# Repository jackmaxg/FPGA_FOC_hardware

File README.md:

# FPGA_FOC_hardware
Hardware for the 6.111 FPGA_FOC project

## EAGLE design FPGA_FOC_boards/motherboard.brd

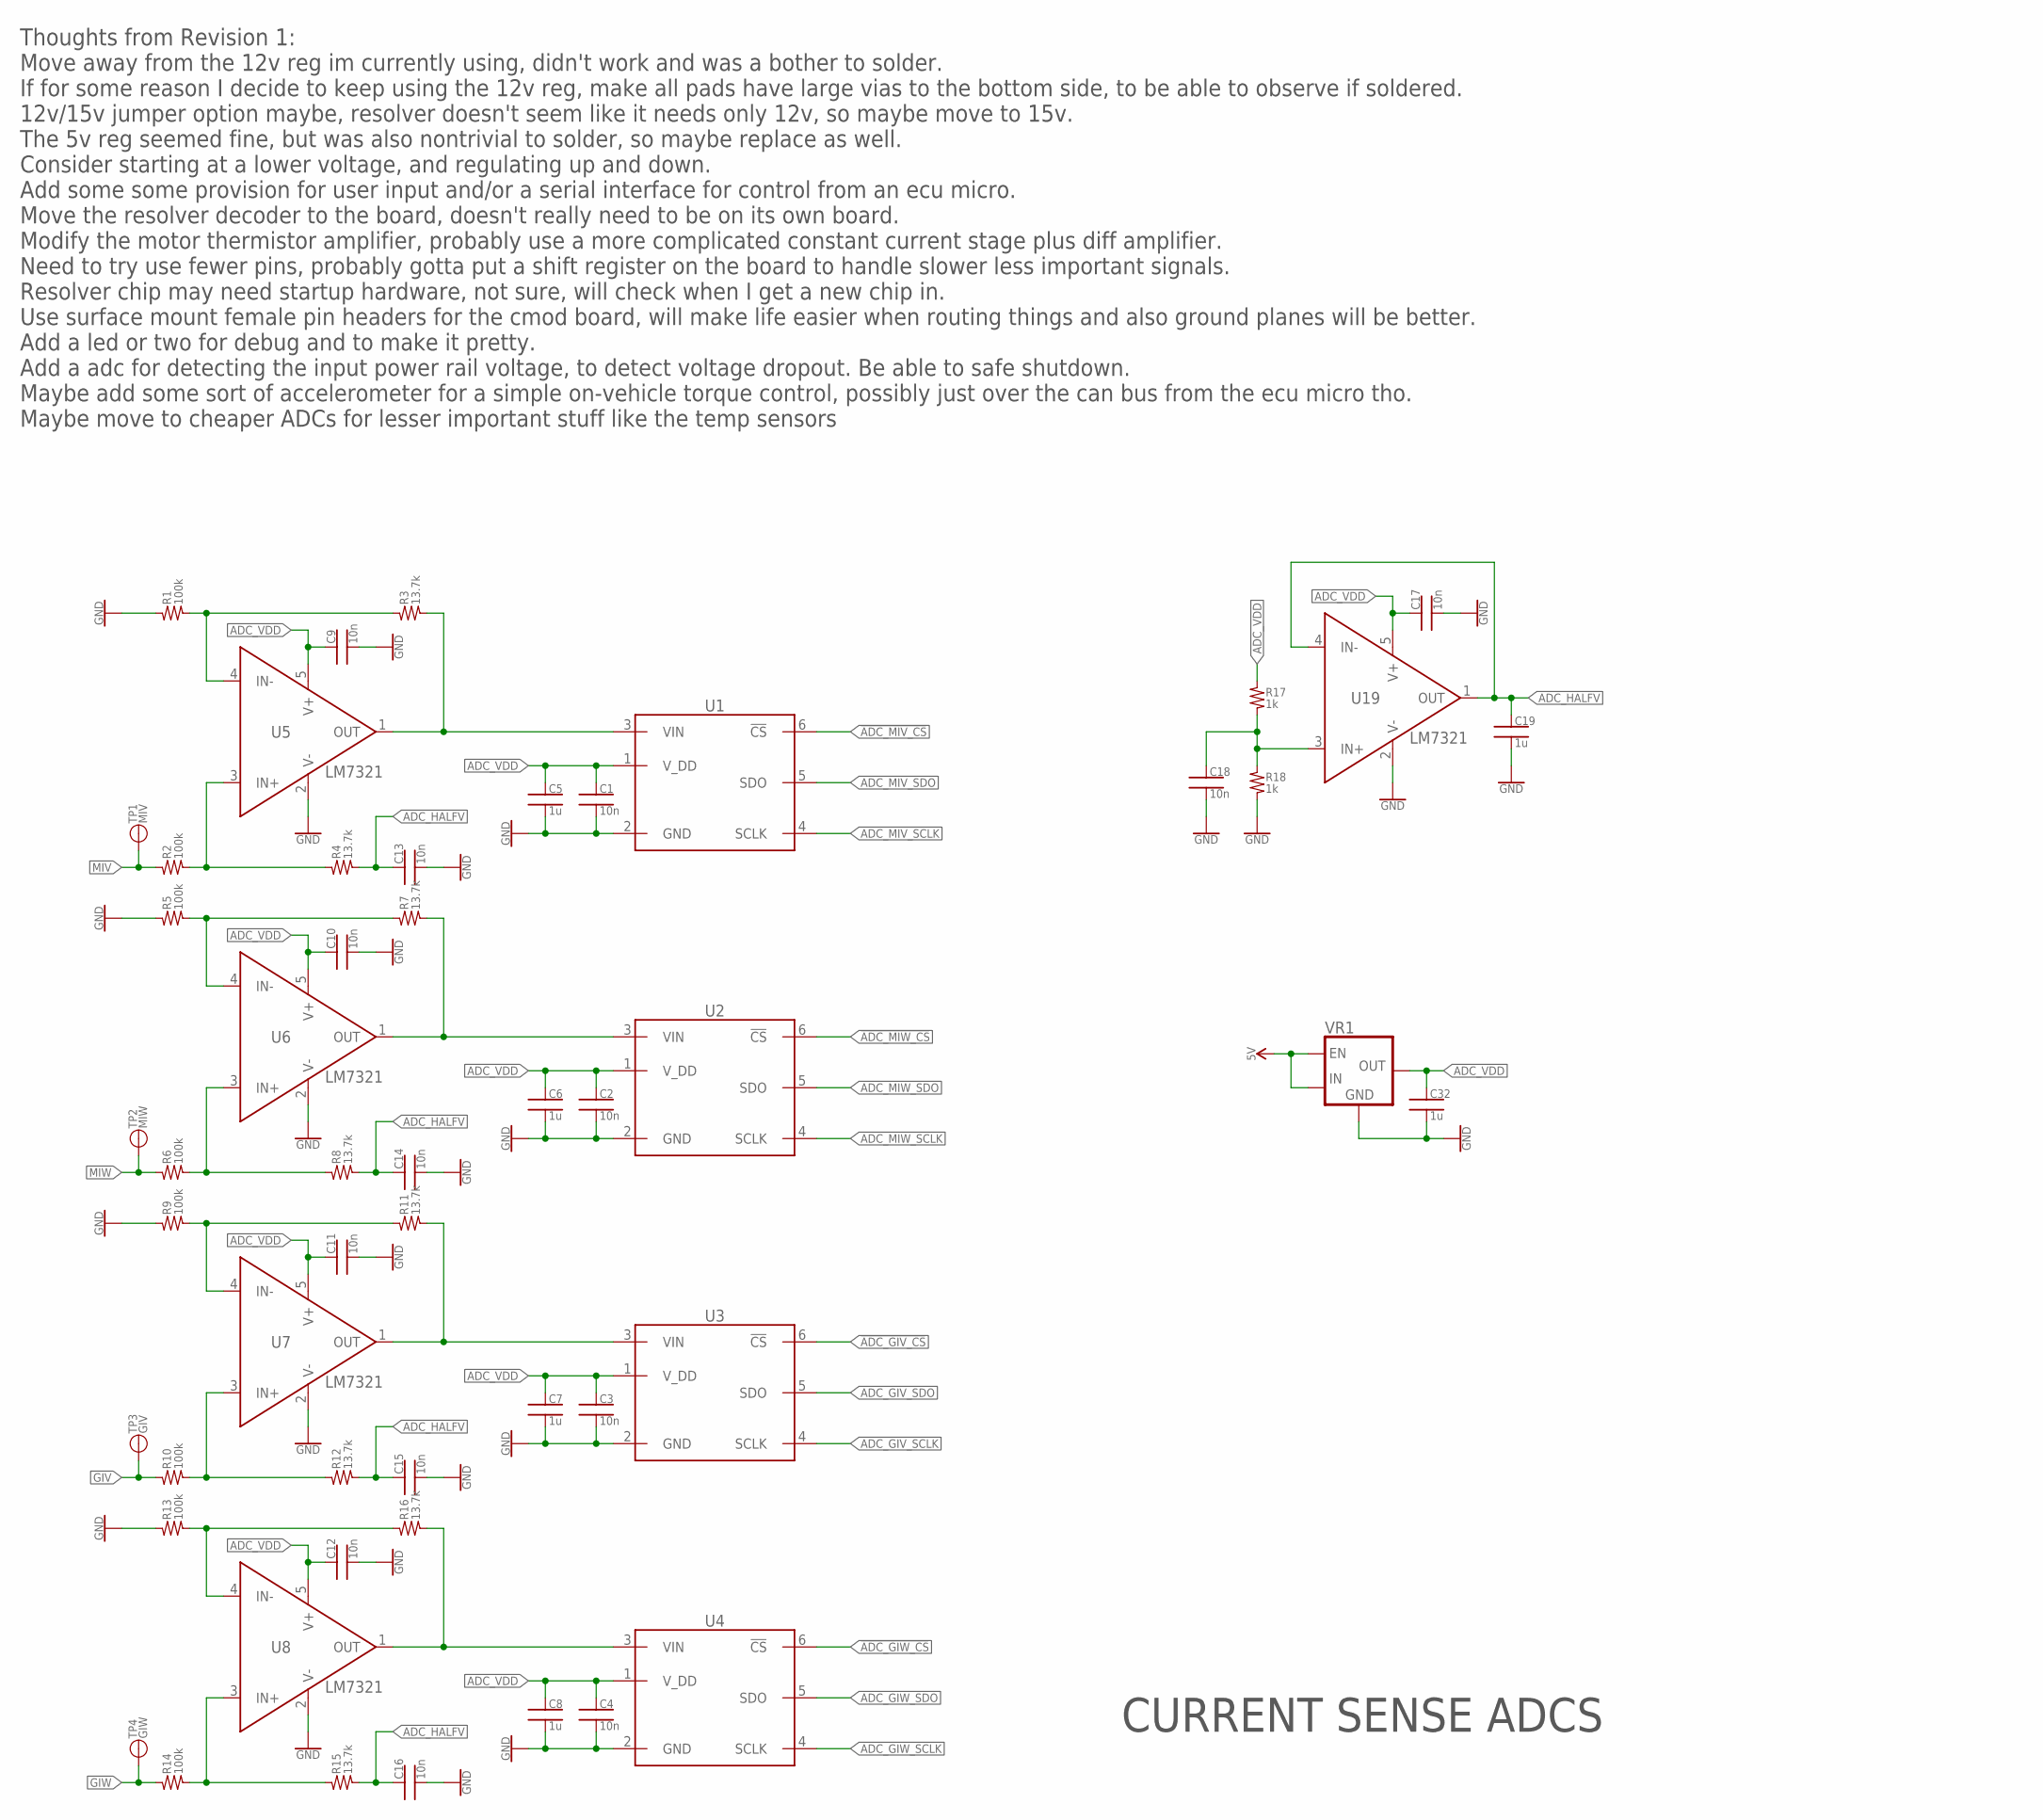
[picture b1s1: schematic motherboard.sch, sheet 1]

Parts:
C1, C2, C3, C4, C9, C10, C11, C12, C13, C14, C15, C16, C17, C18: 10n; 0402
C5, C6, C7, C8, C19, C32: 1u; 0402
R1, R2, R5, R6, R9, R10, R13, R14: 100k; 0402
R3, R4, R7, R8, R11, R12, R15, R16: 13.7k; 0402
R17, R18: 1k; 0402
TP1: MIV; 1X01_50MIL
TP2: MIW; 1X01_50MIL
TP3: GIV; 1X01_50MIL
TP4: GIW; 1X01_50MIL
U1, U2, U3, U4: ADS7883; SOT23-6
U5, U6, U7, U8, U19: LM7321; SOT23-5
VR1: TLV733P_SOT23; SOT23-5

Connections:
5V: VR1.1 (IN), VR1.3 (EN); also elsewhere on the board
!ADC_GIV_CS: U3.6 (!CS); also elsewhere on the board
!ADC_GIW_CS: U4.6 (!CS); also elsewhere on the board
!ADC_MIV_CS: U1.6 (!CS); also elsewhere on the board
!ADC_MIW_CS: U2.6 (!CS); also elsewhere on the board
ADC_GIV_SCLK: U3.4 (SCLK); also elsewhere on the board
ADC_GIV_SDO: U3.5 (SDO); also elsewhere on the board
ADC_GIW_SCLK: U4.4 (SCLK); also elsewhere on the board
ADC_GIW_SDO: U4.5 (SDO); also elsewhere on the board
ADC_HALFV: C13.1, C14.1, C15.1, C16.1, C19.1, R4.2, R8.2, R12.2, R15.2, U19.1 (OUT), U19.4 (IN-)
ADC_HALFV_REF: C18.1, R17.2, R18.1, U19.3 (IN+)
ADC_MIV_SCLK: U1.4 (SCLK); also elsewhere on the board
ADC_MIV_SDO: U1.5 (SDO); also elsewhere on the board
ADC_MIW_SCLK: U2.4 (SCLK); also elsewhere on the board
ADC_MIW_SDO: U2.5 (SDO); also elsewhere on the board
ADC_VDD: C1.1, C2.1, C3.1, C4.1, C5.1, C6.1, C7.1, C8.1, C9.1, C10.1, C11.1, C12.1, C17.1, C32.1, R17.1, U1.1 (V_DD), U2.1 (V_DD), U3.1 (V_DD), U4.1 (V_DD), U5.5 (V+), U6.5 (V+), U7.5 (V+), U8.5 (V+), U19.5 (V+), VR1.5 (OUT); also elsewhere on the board
GIV: R10.1, TP3.1; also elsewhere on the board
GIW: R14.1, TP4.1; also elsewhere on the board
GND: C1.2, C2.2, C3.2, C4.2, C5.2, C6.2, C7.2, C8.2, C9.2, C10.2, C11.2, C12.2, C13.2, C14.2, C15.2, C16.2, C17.2, C18.2, C19.2, C32.2, R1.1, R5.1, R9.1, R13.1, R18.2, U1.2 (GND), U2.2 (GND), U3.2 (GND), U4.2 (GND), U5.2 (V-), U6.2 (V-), U7.2 (V-), U8.2 (V-), U19.2 (V-), VR1.2 (GND), VR1.4 (GND); also elsewhere on the board
MIV: R2.1, TP1.1; also elsewhere on the board
MIW: R6.1, TP2.1; also elsewhere on the board
U5_IN+: R2.2, R4.1, U5.3 (IN+)
U5_IN-: R1.2, R3.1, U5.4 (IN-)
U5_OUT: R3.2, U1.3 (VIN), U5.1 (OUT)
U6_IN+: R6.2, R8.1, U6.3 (IN+)
U6_IN-: R5.2, R7.1, U6.4 (IN-)
U6_OUT: R7.2, U2.3 (VIN), U6.1 (OUT)
U7_IN+: R10.2, R12.1, U7.3 (IN+)
U7_IN-: R9.2, R11.1, U7.4 (IN-)
U7_OUT: R11.2, U3.3 (VIN), U7.1 (OUT)
U8_IN+: R14.2, R15.1, U8.3 (IN+)
U8_IN-: R13.2, R16.1, U8.4 (IN-)
U8_OUT: R16.2, U4.3 (VIN), U8.1 (OUT)

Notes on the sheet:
CURRENT SENSE ADCS
Thoughts from Revision 1: Move away from the 12v reg im currently using, didn't work and was a bother to solder. If for some reason I decide to keep using the 12v reg, make all pads have large vias to the bottom side, to be able to observe if soldered. 12v/15v jumper option maybe, resolver doesn't 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

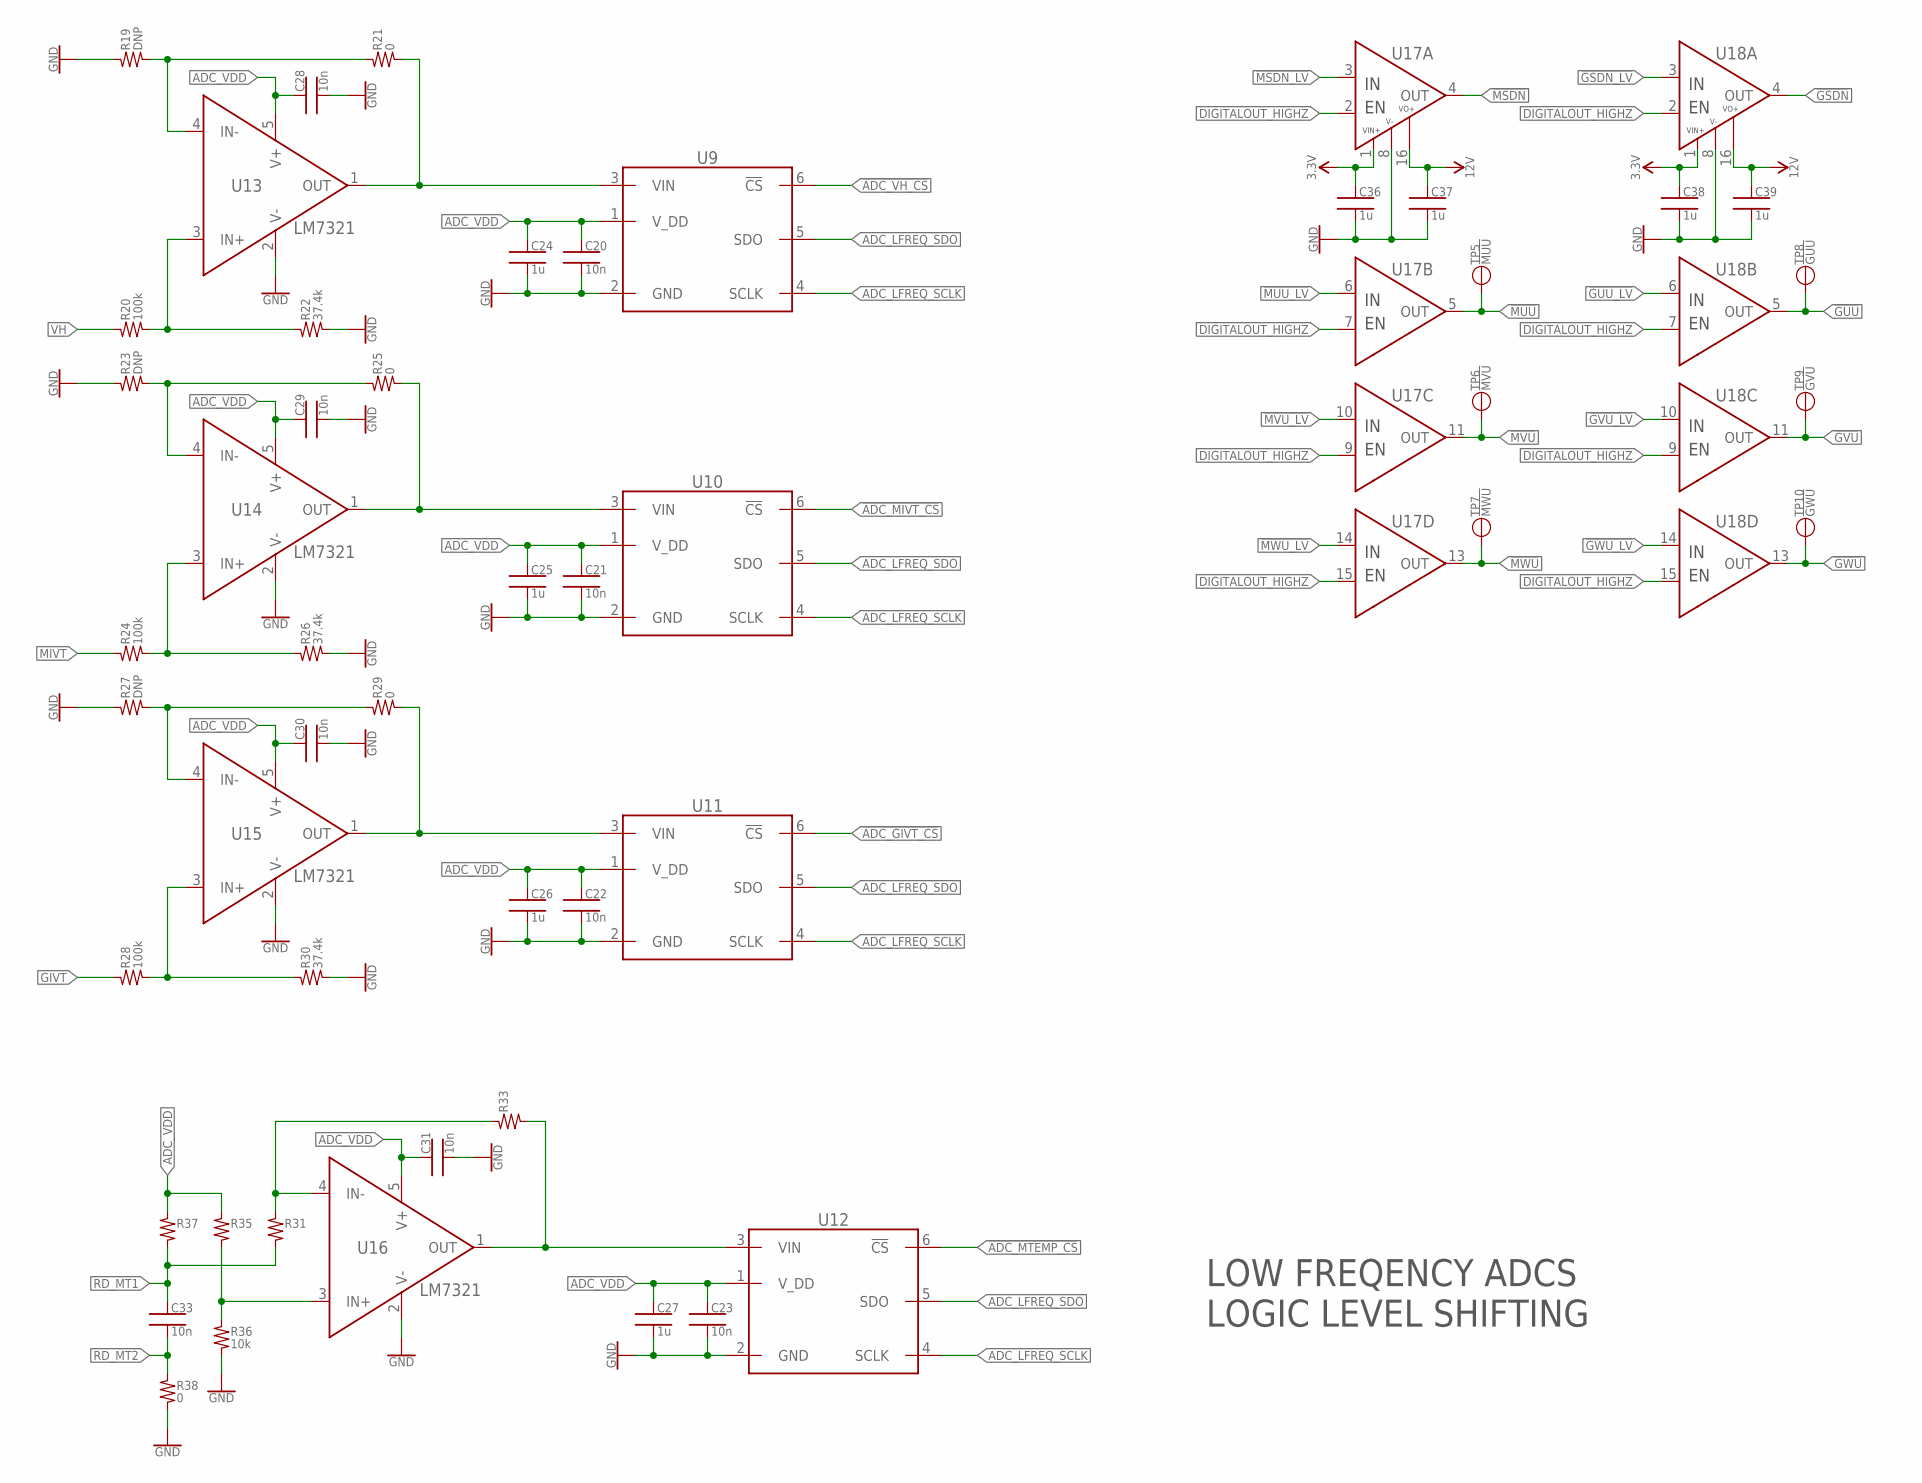
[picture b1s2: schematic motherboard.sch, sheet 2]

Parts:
C20, C21, C22, C23, C28, C29, C30, C31, C33: 10n; 0402
C24, C25, C26, C27, C36, C37, C38, C39: 1u; 0402
R19, R23, R27: DNP; 0402
R20, R24, R28: 100k; 0402
R21, R25, R29, R38: 0; 0402
R22, R26, R30: 37.4k; 0402
R31, R33, R35, R37: RES_SMD_0402; 0402
R36: 10k; 0402
TP5: !MUU; 1X01_50MIL
TP6: !MVU; 1X01_50MIL
TP7: !MWU; 1X01_50MIL
TP8: !GUU; 1X01_50MIL
TP9: !GVU; 1X01_50MIL
TP10: !GWU; 1X01_50MIL
U9, U10, U11, U12: ADS7883; SOT23-6
U13, U14, U15, U16: LM7321; SOT23-5
U17, U18: CD40109BPWR; TSSOP-16

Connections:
3.3V: C36.1, C38.1, U17.1 (VIN+), U18.1 (VIN+); also elsewhere on the board
12V: C37.1, C39.1, U17.16 (VOUT+), U18.16 (VOUT+); also elsewhere on the board
!ADC_GIVT_CS: U11.6 (!CS); also elsewhere on the board
!ADC_MIVT_CS: U10.6 (!CS); also elsewhere on the board
!ADC_MTEMP_CS: U12.6 (!CS); also elsewhere on the board
!ADC_VH_CS: U9.6 (!CS); also elsewhere on the board
!GSDN: U18.4 (OUT); also elsewhere on the board
!GSDN_LV: U18.3 (IN); also elsewhere on the board
!GUU: TP8.1, U18.5 (OUT); also elsewhere on the board
!GUU_LV: U18.6 (IN); also elsewhere on the board
!GVU: TP9.1, U18.11 (OUT); also elsewhere on the board
!GVU_LV: U18.10 (IN); also elsewhere on the board
!GWU: TP10.1, U18.13 (OUT); also elsewhere on the board
!GWU_LV: U18.14 (IN); also elsewhere on the board
!MSDN: U17.4 (OUT); also elsewhere on the board
!MSDN_LV: U17.3 (IN); also elsewhere on the board
!MUU: TP5.1, U17.5 (OUT); also elsewhere on the board
!MUU_LV: U17.6 (IN); also elsewhere on the board
!MVU: TP6.1, U17.11 (OUT); also elsewhere on the board
!MVU_LV: U17.10 (IN); also elsewhere on the board
!MWU: TP7.1, U17.13 (OUT); also elsewhere on the board
!MWU_LV: U17.14 (IN); also elsewhere on the board
ADC_LFREQ_SCLK: U9.4 (SCLK), U10.4 (SCLK), U11.4 (SCLK), U12.4 (SCLK); also elsewhere on the board
ADC_LFREQ_SDO: U9.5 (SDO), U10.5 (SDO), U11.5 (SDO), U12.5 (SDO); also elsewhere on the board
ADC_VDD: C20.1, C21.1, C22.1, C23.1, C24.1, C25.1, C26.1, C27.1, C28.1, C29.1, C30.1, C31.1, R35.1, R37.1, U9.1 (V_DD), U10.1 (V_DD), U11.1 (V_DD), U12.1 (V_DD), U13.5 (V+), U14.5 (V+), U15.5 (V+), U16.5 (V+); also elsewhere on the board
DIGITALOUT_HIGHZ: U17.2 (EN), U17.7 (EN), U17.9 (EN), U17.15 (EN), U18.2 (EN), U18.7 (EN), U18.9 (EN), U18.15 (EN)
GIVT: R28.1; also elsewhere on the board
GND: C20.2, C21.2, C22.2, C23.2, C24.2, C25.2, C26.2, C27.2, C28.2, C29.2, C30.2, C31.2, C36.2, C37.2, C38.2, C39.2, R19.1, R22.2, R23.1, R26.2, R27.1, R30.2, R36.2, R38.2, U9.2 (GND), U10.2 (GND), U11.2 (GND), U12.2 (GND), U13.2 (V-), U14.2 (V-), U15.2 (V-), U16.2 (V-), U17.8 (V-), U18.8 (V-); also elsewhere on the board
MIVT: R24.1; also elsewhere on the board
RD_MT1: C33.1, R31.2, R37.2
RD_MT2: C33.2, R38.1
U13_IN+: R20.2, R22.1, U13.3 (IN+)
U13_IN-: R19.2, R21.1, U13.4 (IN-)
U13_OUT: R21.2, U9.3 (VIN), U13.1 (OUT)
U14_IN+: R24.2, R26.1, U14.3 (IN+)
U14_IN-: R23.2, R25.1, U14.4 (IN-)
U14_OUT: R25.2, U10.3 (VIN), U14.1 (OUT)
U15_IN+: R28.2, R30.1, U15.3 (IN+)
U15_IN-: R27.2, R29.1, U15.4 (IN-)
U15_OUT: R29.2, U11.3 (VIN), U15.1 (OUT)
U16_IN+: R35.2, R36.1, U16.3 (IN+)
U16_IN-: R31.1, R33.1, U16.4 (IN-)
U16_OUT: R33.2, U12.3 (VIN), U16.1 (OUT)
VH: R20.1; also elsewhere on the board

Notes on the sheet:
LOW FREQENCY ADCS LOGIC LEVEL SHIFTING

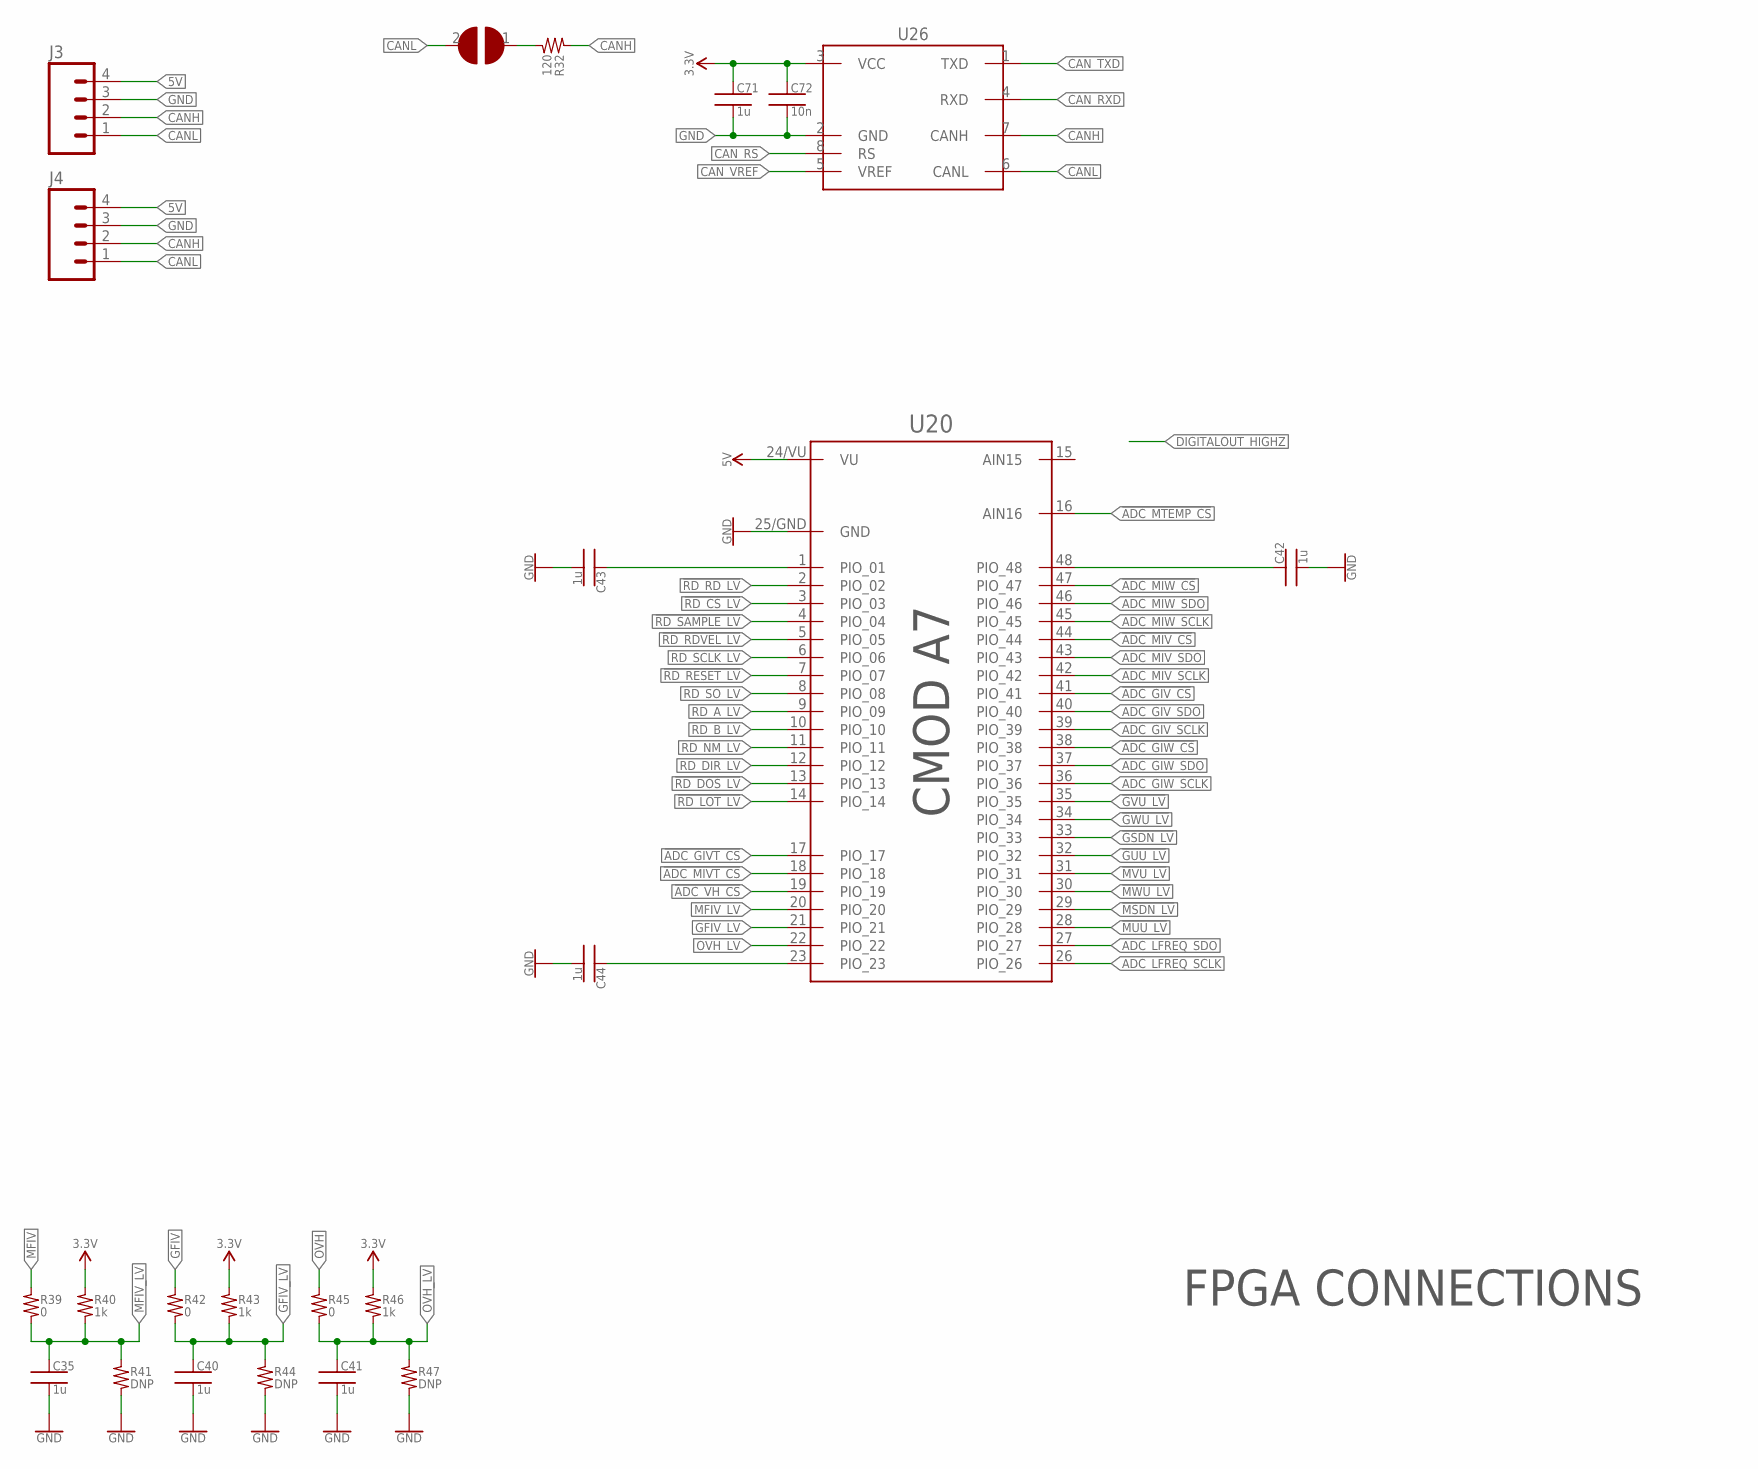
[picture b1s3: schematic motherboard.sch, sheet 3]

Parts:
C35, C40, C41, C42, C43, C44, C71: 1u; 0402
C72: 10n; 0402
J3, J4: SM04B-SRSS-TB
R32: 120; 0402
R39, R42, R45: 0; 0402
R40, R43, R46: 1k; 0402
R41, R44, R47: DNP; 0402
SJ1: SOLDERABLE_JUMPER_1POS_NP; SJ_2S-NO
U20: CMOD_A7; CMOD_A7_DIP
U26: SN65HVD23X; SOIC_8

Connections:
3.3V: C71.1, C72.1, R40.1, R43.1, R46.1, U26.3 (VCC); also elsewhere on the board
5V: J3.4, J4.4, U20.24/VU (VU); also elsewhere on the board
!ADC_GIVT_CS: U20.17 (PIO_17); also elsewhere on the board
!ADC_GIV_CS: U20.41 (PIO_41); also elsewhere on the board
!ADC_GIW_CS: U20.38 (PIO_38); also elsewhere on the board
!ADC_MIVT_CS: U20.18 (PIO_18); also elsewhere on the board
!ADC_MIV_CS: U20.44 (PIO_44); also elsewhere on the board
!ADC_MIW_CS: U20.47 (PIO_47); also elsewhere on the board
!ADC_MTEMP_CS: U20.16 (AIN16); also elsewhere on the board
!ADC_VH_CS: U20.19 (PIO_19); also elsewhere on the board
!GSDN_LV: U20.33 (PIO_33); also elsewhere on the board
!GUU_LV: U20.32 (PIO_32); also elsewhere on the board
!GVU_LV: U20.35 (PIO_35); also elsewhere on the board
!GWU_LV: U20.34 (PIO_34); also elsewhere on the board
!MSDN_LV: U20.29 (PIO_29); also elsewhere on the board
!MUU_LV: U20.28 (PIO_28); also elsewhere on the board
!MVU_LV: U20.31 (PIO_31); also elsewhere on the board
!MWU_LV: U20.30 (PIO_30); also elsewhere on the board
!RD_CS_LV: U20.3 (PIO_03); also elsewhere on the board
!RD_DOS_LV: U20.13 (PIO_13); also elsewhere on the board
!RD_LOT_LV: U20.14 (PIO_14); also elsewhere on the board
!RD_RDVEL_LV: U20.5 (PIO_05); also elsewhere on the board
!RD_RD_LV: U20.2 (PIO_02); also elsewhere on the board
!RD_RESET_LV: U20.7 (PIO_07); also elsewhere on the board
!RD_SAMPLE_LV: U20.4 (PIO_04); also elsewhere on the board
ADC_GIV_SCLK: U20.39 (PIO_39); also elsewhere on the board
ADC_GIV_SDO: U20.40 (PIO_40); also elsewhere on the board
ADC_GIW_SCLK: U20.36 (PIO_36); also elsewhere on the board
ADC_GIW_SDO: U20.37 (PIO_37); also elsewhere on the board
ADC_LFREQ_SCLK: U20.26 (PIO_26); also elsewhere on the board
ADC_LFREQ_SDO: U20.27 (PIO_27); also elsewhere on the board
ADC_MIV_SCLK: U20.42 (PIO_42); also elsewhere on the board
ADC_MIV_SDO: U20.43 (PIO_43); also elsewhere on the board
ADC_MIW_SCLK: U20.45 (PIO_45); also elsewhere on the board
ADC_MIW_SDO: U20.46 (PIO_46); also elsewhere on the board
CANH: J3.2, J4.2, R32.1, U26.7 (CANH)
CANL: J3.1, J4.1, SJ1.2, U26.6 (CANL)
CAN_RS: U26.8 (RS)
CAN_RXD: U26.4 (RXD)
CAN_TXD: U26.1 (TXD)
CAN_VREF: U26.5 (VREF)
GFIV: R42.1; also elsewhere on the board
GFIV_LV: C40.1, R42.2, R43.2, R44.1, U20.21 (PIO_21)
GND: C35.2, C40.2, C41.2, C42.2, C43.2, C44.2, C71.2, C72.2, J3.3, J4.3, R41.2, R44.2, R47.2, U20.25/GND (GND), U26.2 (GND); also elsewhere on the board
MFIV: R39.1; also elsewhere on the board
MFIV_LV: C35.1, R39.2, R40.2, R41.1, U20.20 (PIO_20)
unnamed: R32.2, SJ1.1
OVH: R45.1; also elsewhere on the board
OVH_LV: C41.1, R45.2, R46.2, R47.1, U20.22 (PIO_22)
PIO_01: C43.1, U20.1 (PIO_01)
PIO_23: C44.1, U20.23 (PIO_23)
PIO_48: C42.1, U20.48 (PIO_48)
RD_A_LV: U20.9 (PIO_09); also elsewhere on the board
RD_B_LV: U20.10 (PIO_10); also elsewhere on the board
RD_DIR_LV: U20.12 (PIO_12); also elsewhere on the board
RD_NM_LV: U20.11 (PIO_11); also elsewhere on the board
RD_SCLK_LV: U20.6 (PIO_06); also elsewhere on the board
RD_SO_LV: U20.8 (PIO_08); also elsewhere on the board

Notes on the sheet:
FPGA CONNECTIONS

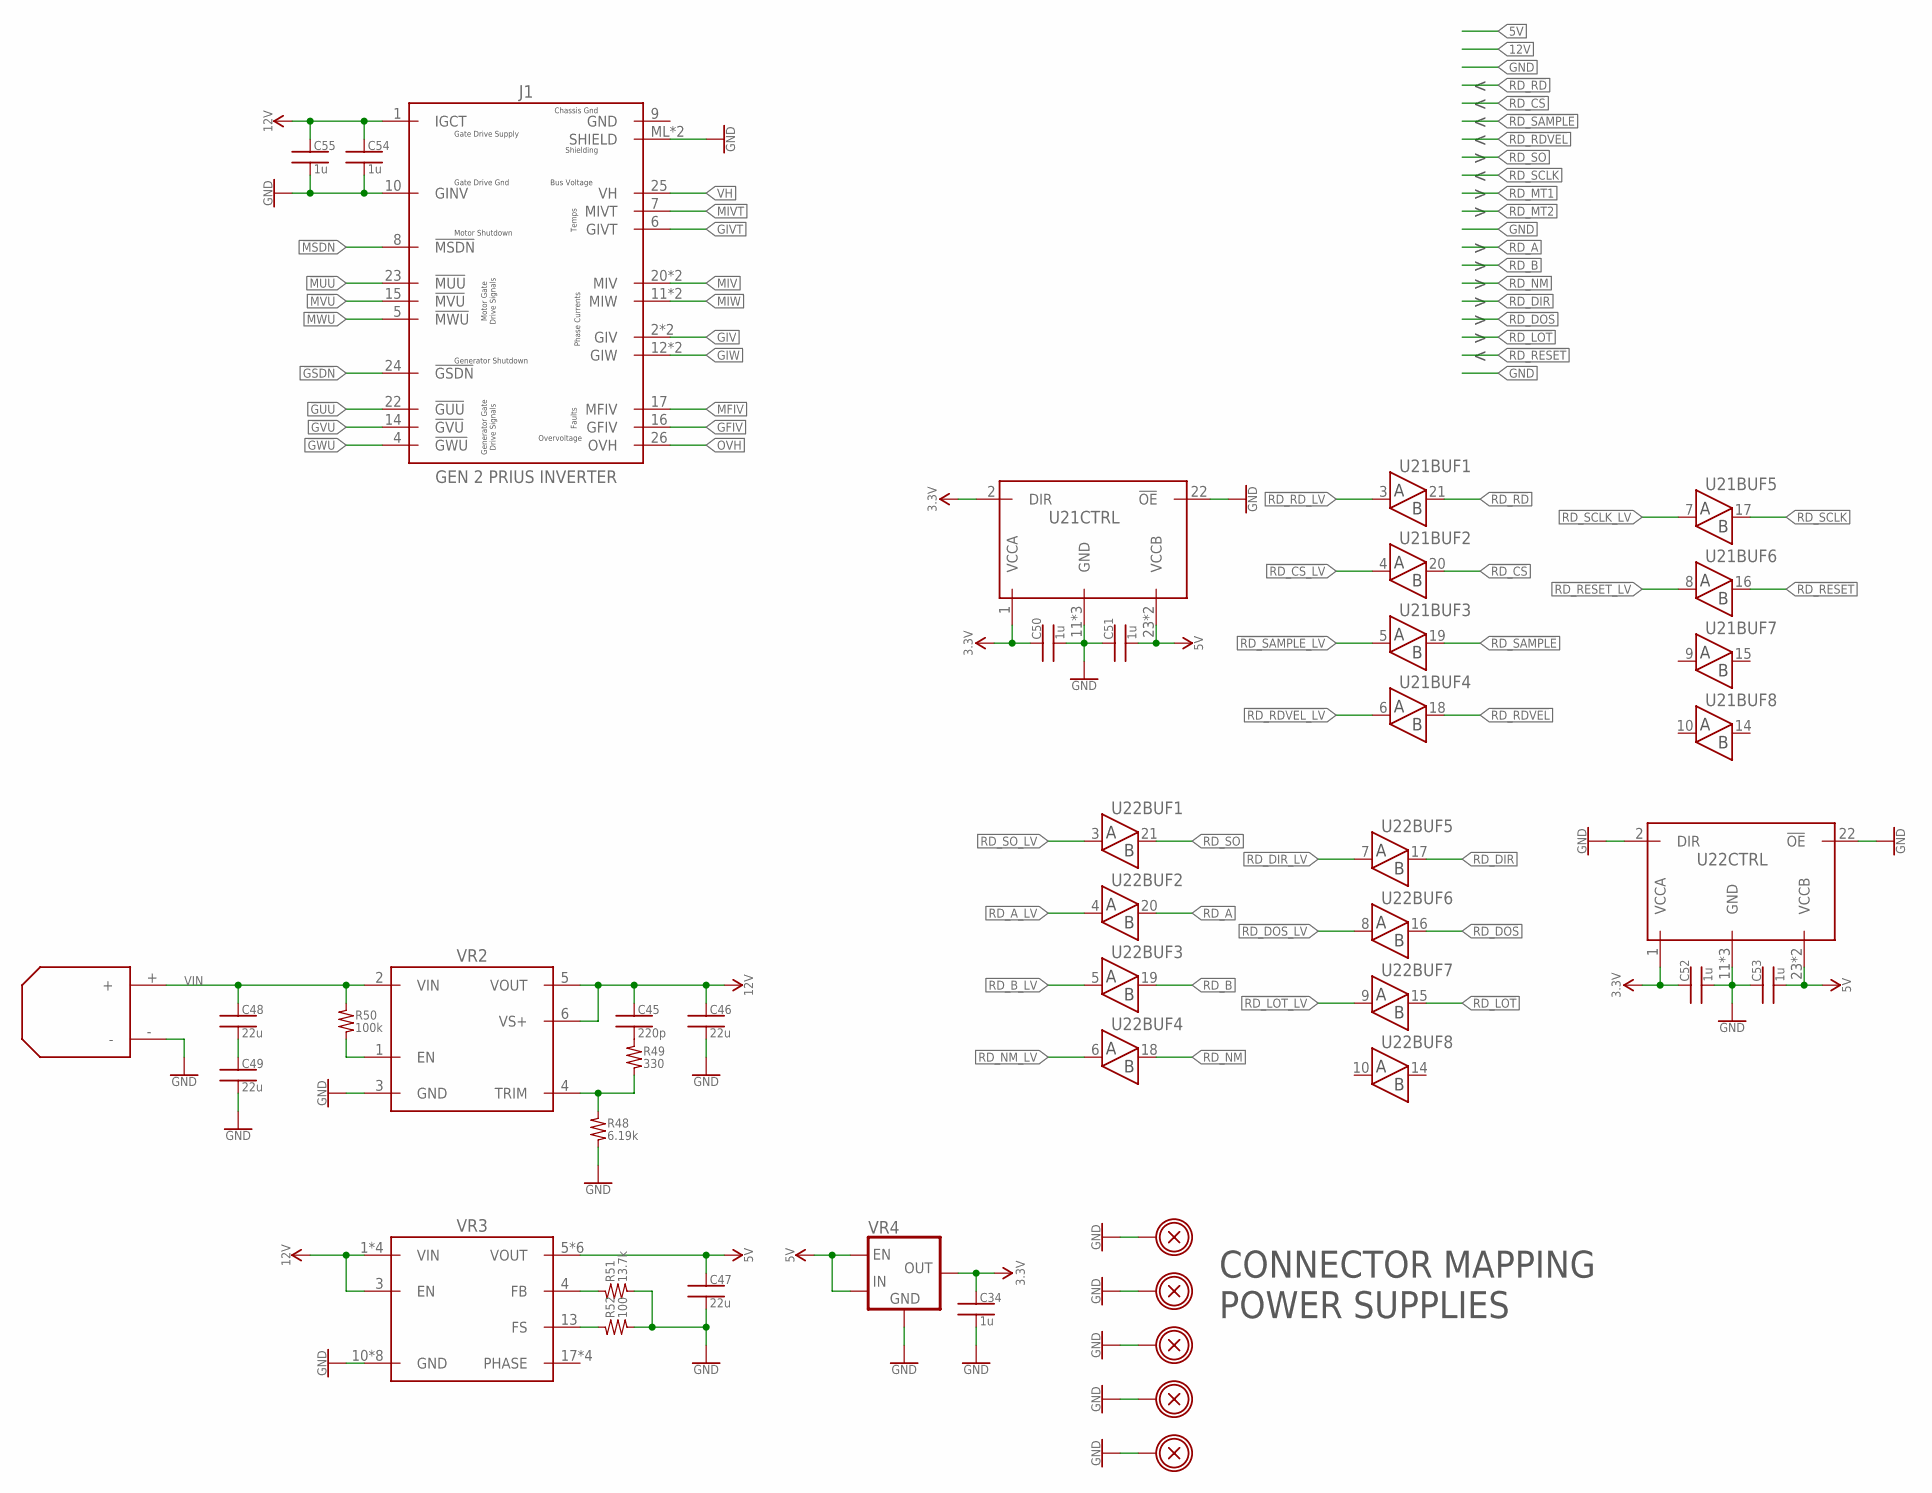
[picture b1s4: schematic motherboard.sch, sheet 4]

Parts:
C34, C50, C51, C52, C53, C54, C55: 1u; 0402
C45: 220p; 0402
C46, C47, C48, C49: 22u; 1210
H1, H2, H3, H4, H5: BOLTHOLE_M3; M3_HOLE
J1: PRIUS_INV_DB26; L17HTHA
R48: 6.19k; 0402
R49: 330; 0402
R50: 100k; 0402
R51: 13.7k; 0402
R52: 100; 0402
U21, U22: 74LVC8T245; TSSOP-24
U$1: XT30; XT30_HORIZONTAL
VR2: PROLYNX
VR3: MUN24AD03-SM; UPOL_PWR_MODULE
VR4: TLV733P_SOT23; SOT23-5

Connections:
3.3V: C34.1, C50.1, C52.1, U21.1 (VCCA), U21.2 (DIR), U22.1 (VCCA), VR4.5 (OUT); also elsewhere on the board
5V: C47.1, C51.2, C53.2, U21.23 (VCCB), U21.24 (VCCB), U22.23 (VCCB), U22.24 (VCCB), VR3.5 (VOUT), VR3.6 (VOUT), VR3.7 (VOUT), VR3.8 (VOUT), VR3.9 (VOUT), VR3.24 (VOUT), VR4.1 (IN), VR4.3 (EN); also elsewhere on the board
12V: C45.1, C46.1, C54.1, C55.1, J1.1 (IGCT), VR2.5 (VOUT), VR2.6 (VS+), VR3.1 (VIN), VR3.2 (VIN), VR3.3 (EN), VR3.20 (VIN), VR3.21 (VIN); also elsewhere on the board
!GSDN: J1.24 (!GSDN); also elsewhere on the board
!GUU: J1.22 (!GUU); also elsewhere on the board
!GVU: J1.14 (!GVU); also elsewhere on the board
!GWU: J1.4 (!GWU); also elsewhere on the board
!MSDN: J1.8 (!MSDN); also elsewhere on the board
!MUU: J1.23 (!MUU); also elsewhere on the board
!MVU: J1.15 (!MVU); also elsewhere on the board
!MWU: J1.5 (!MWU); also elsewhere on the board
!RD_CS: U21.20 (B); also elsewhere on the board
!RD_CS_LV: U21.4 (A); also elsewhere on the board
!RD_DOS: U22.16 (B); also elsewhere on the board
!RD_DOS_LV: U22.8 (A); also elsewhere on the board
!RD_LOT: U22.15 (B); also elsewhere on the board
!RD_LOT_LV: U22.9 (A); also elsewhere on the board
!RD_RD: U21.21 (B); also elsewhere on the board
!RD_RDVEL: U21.18 (B); also elsewhere on the board
!RD_RDVEL_LV: U21.6 (A); also elsewhere on the board
!RD_RD_LV: U21.3 (A); also elsewhere on the board
!RD_RESET: U21.16 (B); also elsewhere on the board
!RD_RESET_LV: U21.8 (A); also elsewhere on the board
!RD_SAMPLE: U21.19 (B); also elsewhere on the board
!RD_SAMPLE_LV: U21.5 (A); also elsewhere on the board
GFIV: J1.16 (GFIV); also elsewhere on the board
GIV: J1.2 (GIV), J1.3 (GIV); also elsewhere on the board
GIVT: J1.6 (GIVT); also elsewhere on the board
GIW: J1.12 (GIW), J1.13 (GIW); also elsewhere on the board
GND: C34.2, C46.2, C47.2, C49.2, C50.2, C51.1, C52.2, C53.1, C54.2, C55.2, H1.P, H2.P, H3.P, H4.P, H5.P, J1.10 (GINV), J1.ML (SHIELD), J1.MR (SHIELD), R48.2, R51.2, R52.2, U21.11 (GND), U21.12 (GND), U21.13 (GND), U21.22 (!OE), U22.2 (DIR), U22.11 (GND), U22.12 (GND), U22.13 (GND), U22.22 (!OE), U$1.-, VR2.3 (GND), VR3.10 (GND), VR3.11 (GND), VR3.12 (GND), VR3.14 (GND), VR3.15 (GND), VR3.16 (GND), VR3.23 (GND), VR3.25 (GND), VR4.2 (GND), VR4.4 (GND); also elsewhere on the board
MFIV: J1.17 (MFIV); also elsewhere on the board
MIV: J1.20 (MIV), J1.21 (MIV); also elsewhere on the board
MIVT: J1.7 (MIVT); also elsewhere on the board
MIW: J1.11 (MIW), J1.19 (MIW); also elsewhere on the board
unnamed: C45.2, R49.1
OVH: J1.26 (OVH); also elsewhere on the board
RD_A: U22.20 (B); also elsewhere on the board
RD_A_LV: U22.4 (A); also elsewhere on the board
RD_B: U22.19 (B); also elsewhere on the board
RD_B_LV: U22.5 (A); also elsewhere on the board
RD_DIR: U22.17 (B); also elsewhere on the board
RD_DIR_LV: U22.7 (A); also elsewhere on the board
RD_NM: U22.18 (B); also elsewhere on the board
RD_NM_LV: U22.6 (A); also elsewhere on the board
RD_SCLK: U21.17 (B); also elsewhere on the board
RD_SCLK_LV: U21.7 (A); also elsewhere on the board
RD_SO: U22.21 (B); also elsewhere on the board
RD_SO_LV: U22.3 (A); also elsewhere on the board
VH: J1.25 (VH); also elsewhere on the board
VIN: C48.1, R50.1, U$1.+, VR2.2 (VIN)
VIN_BYP_MID: C48.2, C49.1
VR2_EN: R50.2, VR2.1 (EN)
VR2_TRIM: R48.1, R49.2, VR2.4 (TRIM)
VR3_FB: R51.1, VR3.4 (FB)
VR3_FS: R52.1, VR3.13 (FS)

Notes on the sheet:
CONNECTOR MAPPING POWER SUPPLIES
